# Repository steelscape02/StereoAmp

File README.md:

# StereoAmp
Stereo Amplifier built in KiCad with a Baxandall Tone Control system

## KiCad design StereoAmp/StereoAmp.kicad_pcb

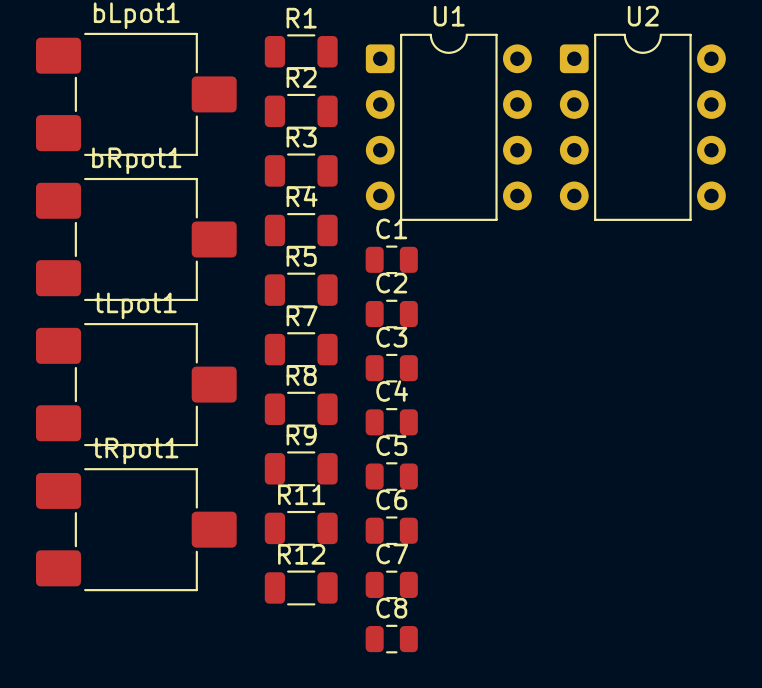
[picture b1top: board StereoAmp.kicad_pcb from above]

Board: 2 copper layers, 24 parts (0 on the bottom side), 21 nets, no tracks yet.

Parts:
C1, C3: 47nF; C_0805_2012Metric
C2, C4, C6, C8: 3.3nF; C_0805_2012Metric
C5, C7: 33nF; C_0805_2012Metric
R1, R2, R3, R4, R5, R9: 4k; R_1206_3216Metric
R7, R8, R11, R12: 820; R_1206_3216Metric
U1, U2: NE5532; DIP-8_W7.62mm
bLpot1: 10k; Potentiometer_ACP_CA6-VSMD_Vertical
bRpot1: 10k; Potentiometer_ACP_CA6-VSMD_Vertical
tLpot1: 10k; Potentiometer_ACP_CA6-VSMD_Vertical
tRpot1: 10k; Potentiometer_ACP_CA6-VSMD_Vertical

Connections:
/bLout: R2.2, U2.1
/bRout: R4.2, U2.7
/tLin: R5.1, R7.1
/tLout: R8.2, U1.1
/tRin: R9.1, R11.1
/tRout: R12.2, U1.7
GND: U1.2 (-), U1.6 (-), U2.2 (-), U2.6 (-)
unnamed: C1.1, C2.1, R1.2, bLpot1.3
unnamed: C1.2, C2.2, R2.1, bLpot1.1
unnamed: C3.1, C4.1, R3.2, bRpot1.3
unnamed: C3.2, C4.2, R4.1, bRpot1.1
unnamed: C5.1, C6.1, tLpot1.2
unnamed: C7.1, C8.1, tRpot1.2
unnamed: R7.2, tLpot1.3
unnamed: R8.1, tLpot1.1
unnamed: R11.2, tRpot1.3
unnamed: R12.1, tRpot1.1
unnamed: C5.2, C6.2, R5.2, U1.3 (+)
unnamed: C7.2, C8.2, R9.2, U1.5 (+)
unnamed: U2.3 (+), bLpot1.2
unnamed: U2.5 (+), bRpot1.2

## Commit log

2026-06-28 Tone Control rework
    Designator work in tone control
